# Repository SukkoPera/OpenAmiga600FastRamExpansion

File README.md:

# OpenAmiga600FastRamExpansion
OpenAmiga600FastRamExpansion is an Open Hardware 4 MB Fast RAM Expansion for the Commodore Amiga 600 Computer.

### Summary
Most low-end Amiga models only came with *Chip RAM*. "Big Box" models allowed for a different type of memory to be installed, known as *Fast RAM*, where *fast* means that it's dedicated to the main processor, so that it doesn't have to compete with the other chips in order to gain access to it (as is the case with Chip RAM). While both Chip and Fast RAM are limited in size, you can have at least a few MB of the latter on all Amigas (usually up to 8), while the former can never exceed 2 MB.

OpenAmiga600FastRamExpansion will allow you to add 4 MB of Fast RAM to your Amiga 600. This way you will be able to run more applications at once and more quickly. If you combine it with [a chip RAM expansion](https://github.com/SukkoPera/OpenAmiga600RamExpansion), you will also be able to run almost all games supported by WHDLoad, pushing the smallest of the Amigas to its limits. The Fast RAM will be mapped to `$200000-$5fffff`, which means it will not interfere with the PCMCIA address space.

Note that the A600 was not originally designed to support a Fast RAM expansion, which means Commodore didn't provide any connector for it. In theory it could be sandwiched between the CPU and mainboard, as usually done on A500s, but in the A600 the CPU is soldered directly to the mainboard and cannot be removed. Thus the only way to install it is to clip it over the CPU, using a PLCC socket placed upside-down. PLCC sockets are not meant to be used this way, so this is really a bit of a hack and might not even work in all cases. Space around the CPU is quite limited, hence the odd shape of this board.

OpenAmiga600FastRamExpansion is basically a clone of [a RAM expansion produced by Kipper2K a few years ago](http://eab.abime.net/showthread.php?t=64218), based on [an earlier design by lvd/NedoPC](http://lvd.nedopc.com/Projects/a600_8mb/index.html). He has since stopped producing and selling these cards and I thought it was a pity that he didn't open his designs and actually took all of them down, as this card is quite cheap to build and really useful. So I set about recreating it from scratch. Kipper2K has also made other expansions, including an 8 MB version of this card, but I chose to work on this one as it was simpler and probably enough for most uses. Other cards might come in the future.

### Memory Compatibility
The required RAM Type is 16 Mbit (1M×16) DRAM in the SOJ-42 package with up to 70-80 ns access time. It is 5v-only DRAM (not SDRAM!) often found in old 72-pin SIMMs, EDO chips might work or not. All chips having *8160* in their part number should be OK.

See [OpenAmiga500FastRamExpansion](https://github.com/SukkoPera/OpenAmiga500FastRamExpansion#memory-compatibility) for a compatibility list.

### Assembly and Installation
Open your A600, doing your best not to crack any of the small tabs that hold the case together. If your A600 has the top part of the shielding, remove it and store it somewhere, as you will not be able to put it back in place when the expansion is installed. The same goes for the HD cradle, sorry.

Lots of A600s (and of A1200s, for the record) have issues with leaking electrolytic capacitors, therefore I really recommend to inspect them first, while you have your Amiga open. They might be leaking even if your Amiga shows no problems and when it finally will, it might be too late (= expensive) to salvage it. So, if you notice any white or brownish marks around those shiny metal cylinders, get them replaced. It is NOT an easy thing to do and you need some decent tools anyway, so I really recommend to contact a professional, there are many people on Amiga forums offering this kind of service.

I suggest soldering the RAM chips first: these can either be soldered directly to the board or installed in sockets. While soldering the chips might not be trivial for the unexperienced, sockets for the SOJ-42 package are hard to find and not really easier to solder either, so the choice is up to you.

Next you should solder all the remaining surface mount components, first on the top side and then on the bottom side. Keep the CPLD and CPU socket last. Normally it is not necessary to mount all the decoupling capacitors for the RAM: I usually skip C4 and C7. Maybe capacitor C13 can be left out as well, your choice. R4 should be chosen according to the particular led you will be using for LD1. Actually you are free to skip LD1 and R4 altogether, if you hate power LEDs.

Before soldering the CPU socket you will need to rework it a bit if you want a really good fit: get some sandpaper and follow [these instructions](SocketRework.md). After it has been soldered, you can cut the bottom of it so that the window in the PCB continues through the socket. Most sockets will already have holes on the bottom that will make this operation easier. This will allow you to install a 14x14mm heatsink on the CPU, which might be a good idea since placing this board over the CPU will somewhat reduce the heat dissipation capabilities of the chip. Make sure to use good thermal adhesive/glue, otherwise you risk to make the dissipation even worse.

When you are done with the soldering you will need to program the CPLD. Whenever you do so, **make sure to carefully remove the board from your Amiga, or you might risk damaging it**. You can find the firmware [here](https://github.com/SukkoPera/OpenAmiga500FastRamExpansion/tree/master/firmware), along with instructions on how to flash it. Make sure you use the 4 MB version! You can provide power through the pads of C13 if you need to do so.

You are finally ready to install the expansion in your A600 but, before you do this, I suggest to clean the CPU pins using contact cleaner or isopropyl alcool and a toothbrush or cotton swabs, as all sorts of gunk will have probably gathered on them over the years. Let them dry well, then place the expansion over the CPU with the correct orientation and push it down firmly until it feels solidly in place. There should be no need to use the Force&trade;.

Before reassembling your case, I recommend to run [SysTest/Amiga Test Kit](https://github.com/keirf/Amiga-Stuff). Use the Memory option (<kbd>F1</kbd>), it must show 4 MB of Fast RAM. Then start the Memory Test (<kbd>F1</kbd> again) and let it run for 50-100 rounds: if it doesn't find any errors, you are probably good to go. If you get any errors, power off your computer and try to give the expansion a better fit, by pushing it further down or slightly twisting it back and forth.

It might happen that the board slowly works its way out of the socket over time. To avoid this you can anchor it to the mainboard using the hole to the left of the CPU, which should align with one of the holes for the HD cradle legs. If you have a 3D printer, another option is using [this nice frame designed by blekihun](https://www.thingiverse.com/thing:4824656).

Note that, as already mentioned, PLCC sockets are not meant to be used this way, which means that the contact quality degrades a bit with every insertion or removal of the board. So, try not to remove it unnecessarily. If you find that the contact has degraded so much that the machine is no longer stable, replace the socket with a new one.

### License
The OpenAmiga600FastRamExpansion documentation, including the design itself, is copyright &copy; SukkoPera 2019.

OpenAmiga600FastRamExpansion is Open Hardware licensed under the [CERN OHL v. 1.2](http://ohwr.org/cernohl).

You may redistribute and modify this documentation under the terms of the CERN OHL v.1.2. This documentation is distributed *as is* and WITHOUT ANY EXPRESS OR IMPLIED WARRANTIES whatsoever with respect to its functionality, operability or use, including, without limitation, any implied warranties OF MERCHANTABILITY, SATISFACTORY QUALITY, FITNESS FOR A PARTICULAR PURPOSE or infringement. We expressly disclaim any liability whatsoever for any direct, indirect, consequential, incidental or special damages, including, without limitation, lost revenues, lost profits, losses resulting from business interruption or loss of data, regardless of the form of action or legal theory under which the liability may be asserted, even if advised of the possibility or likelihood of such damages.

A copy of the full license is included in file [LICENSE.pdf](LICENSE.pdf), please refer to it for applicable conditions. In order to properly deal with its terms, please see file [LICENSE_HOWTO.pdf](LICENSE_HOWTO.pdf).

The contact points for information about manufactured Products (see section 4.2) are listed in file [PRODUCT.md](PRODUCT.md).

Any modifications made by Licensees (see section 3.4.b) shall be recorded in file [CHANGES.md](CHANGES.md).

The Documentation Location of the original project is https://github.com/SukkoPera/OpenAmiga600FastRamExpansion/.

### Support the Project
Since the project is open you are free to get the PCBs made by your preferred manufacturer, however in case you want to support the development, you can order them from PCBWay through this link:

You get my gratitude and cheap, professionally-made and good quality PCBs, I get some credit that will help with this and [other projects](https://www.pcbway.com/project/member/shareproject/?bmbid=41100). You won't even have to worry about the various PCB options, it's all pre-configured for you!

Also, if you still have to register to that site, [you can use this link](https://www.pcbway.com/setinvite.aspx?inviteid=41100) to get some bonus initial credit (and yield me some more).

Again, if you want to use another manufacturer, feel free to, don't feel obligated :). But then you can buy me a coffee if you want:

### Thanks
- lvd for the initial design
- Kipper2K for making his boards
- majinga for helping with the testing

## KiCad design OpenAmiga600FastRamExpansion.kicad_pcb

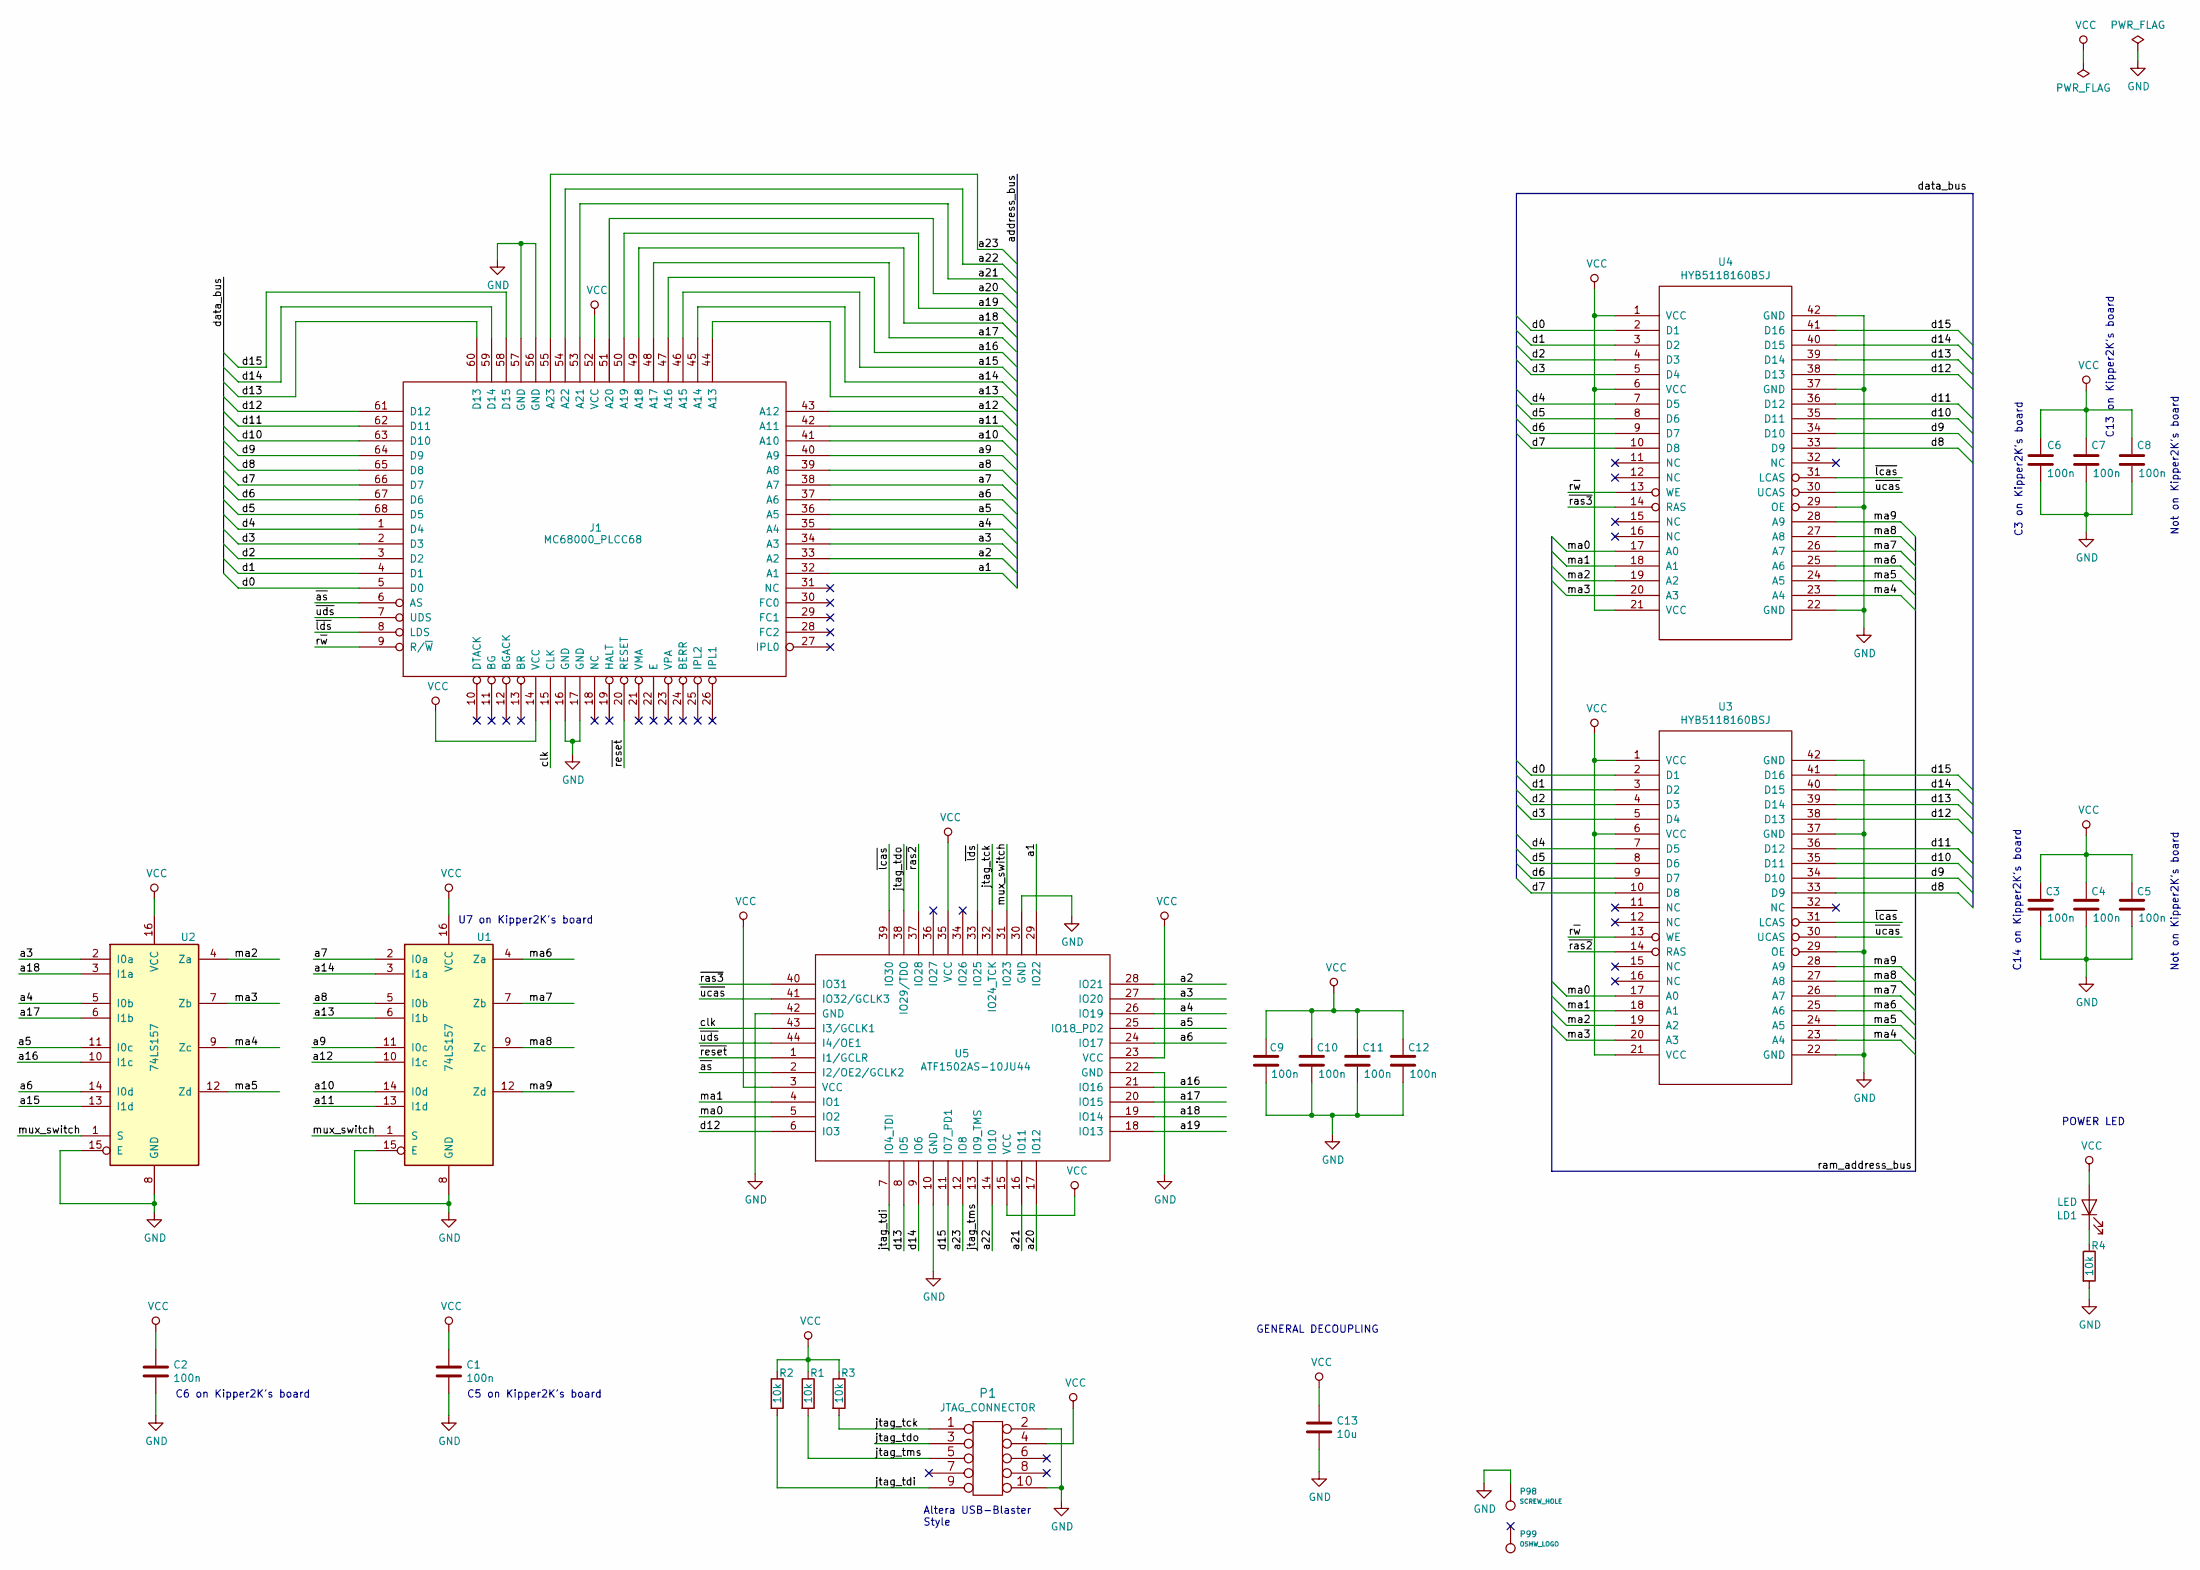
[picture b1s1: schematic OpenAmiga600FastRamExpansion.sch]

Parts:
C1, C2, C3, C4, C5, C6, C7, C8, C9, C10, C11, C12: 100n; C_0805_2012Metric_Pad1.15x1.40mm_HandSolder
C13: 10u; CP_Radial_D5.0mm_P2.00mm
J1: MC68000_PLCC68; PLCC-68_THT-SocketUpsideDown
LD1: LED; LED_0805_HandSoldering_ModSilkS
P1: JTAG_CONNECTOR; IDC-Header_2x05_P2.54mm_Vertical
P98: SCREW_HOLE; MountingHole_2.5mm_Pad_Via
P99: OSHW_LOGO; OSHW-Logo2_7.3x6mm_Copper
R1, R2, R3, R4: 10k; R_0805_2012Metric_Pad1.15x1.40mm_HandSolder
U1, U2: 74LS157; SOIC-16_3.9x9.9mm_P1.27mm
U3, U4: HYB5118160BSJ; SOJ-42-LongPads
U5: ATF1502AS-10JU44; PLCC-44_THT-Socket

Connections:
/a1: J1.32 (A1), U5.29 (IO22)
/a2: J1.33 (A2), U5.28 (IO21)
/a3: J1.34 (A3), U2.2 (I0a), U5.27 (IO20)
/a4: J1.35 (A4), U2.5 (I0b), U5.26 (IO19)
/a5: J1.36 (A5), U2.11 (I0c), U5.25 (IO18_PD2)
/a6: J1.37 (A6), U2.14 (I0d), U5.24 (IO17)
/a7: J1.38 (A7), U1.2 (I0a)
/a8: J1.39 (A8), U1.5 (I0b)
/a9: J1.40 (A9), U1.11 (I0c)
/a10: J1.41 (A10), U1.14 (I0d)
/a11: J1.42 (A11), U1.13 (I1d)
/a12: J1.43 (A12), U1.10 (I1c)
/a13: J1.44 (A13), U1.6 (I1b)
/a14: J1.45 (A14), U1.3 (I1a)
/a15: J1.46 (A15), U2.13 (I1d)
/a16: J1.47 (A16), U2.10 (I1c), U5.21 (IO16)
/a17: J1.48 (A17), U2.6 (I1b), U5.20 (IO15)
/a18: J1.49 (A18), U2.3 (I1a), U5.19 (IO14)
/a19: J1.50 (A19), U5.18 (IO13)
/a20: J1.51 (A20), U5.17 (IO12)
/a21: J1.53 (A21), U5.16 (IO11)
/a22: J1.54 (A22), U5.14 (IO10)
/a23: J1.55 (A23), U5.12 (IO8)
/clk: J1.15 (CLK), U5.43 (I3/GCLK1)
/d0: J1.5 (D0), U3.2 (D1), U4.2 (D1)
/d1: J1.4 (D1), U3.3 (D2), U4.3 (D2)
/d2: J1.3 (D2), U3.4 (D3), U4.4 (D3)
/d3: J1.2 (D3), U3.5 (D4), U4.5 (D4)
/d4: J1.1 (D4), U3.7 (D5), U4.7 (D5)
/d5: J1.68 (D5), U3.8 (D6), U4.8 (D6)
/d6: J1.67 (D6), U3.9 (D7), U4.9 (D7)
/d7: J1.66 (D7), U3.10 (D8), U4.10 (D8)
/d8: J1.65 (D8), U3.33 (D9), U4.33 (D9)
/d9: J1.64 (D9), U3.34 (D10), U4.34 (D10)
/d10: J1.63 (D10), U3.35 (D11), U4.35 (D11)
/d11: J1.62 (D11), U3.36 (D12), U4.36 (D12)
/d12: J1.61 (D12), U3.38 (D13), U4.38 (D13), U5.6 (IO3)
/d13: J1.60 (D13), U3.39 (D14), U4.39 (D14), U5.8 (IO5)
/d14: J1.59 (D14), U3.40 (D15), U4.40 (D15), U5.9 (IO6)
/d15: J1.58 (D15), U3.41 (D16), U4.41 (D16), U5.11 (IO7_PD1)
/jtag_tck: P1.1, R3.2, U5.32 (IO24_TCK)
/jtag_tdi: P1.9, R2.2, U5.7 (IO4_TDI)
/jtag_tdo: P1.3, U5.38 (IO29/TDO)
/jtag_tms: P1.5, R1.2, U5.13 (IO9_TMS)
/ma0: U3.17 (A0), U4.17 (A0), U5.5 (IO2)
/ma1: U3.18 (A1), U4.18 (A1), U5.4 (IO1)
/ma2: U2.4 (Za), U3.19 (A2), U4.19 (A2)
/ma3: U2.7 (Zb), U3.20 (A3), U4.20 (A3)
/ma4: U2.9 (Zc), U3.23 (A4), U4.23 (A4)
/ma5: U2.12 (Zd), U3.24 (A5), U4.24 (A5)
/ma6: U1.4 (Za), U3.25 (A6), U4.25 (A6)
/ma7: U1.7 (Zb), U3.26 (A7), U4.26 (A7)
/ma8: U1.9 (Zc), U3.27 (A8), U4.27 (A8)
/ma9: U1.12 (Zd), U3.28 (A9), U4.28 (A9)
/mux_switch: U1.1 (S), U2.1 (S), U5.31 (IO23)
/r~w: J1.9 (R/~W), U3.13 (WE), U4.13 (WE)
/~as: J1.6 (AS), U5.2 (I2/OE2/GCLK2)
/~lcas: U3.31 (LCAS), U4.31 (LCAS), U5.39 (IO30)
/~lds: J1.8 (LDS), U5.33 (IO25)
/~ras2: U3.14 (RAS), U5.37 (IO28)
/~ras3: U4.14 (RAS), U5.40 (IO31)
/~reset: J1.20 (RESET), U5.1 (I1/GCLR)
/~ucas: U3.30 (UCAS), U4.30 (UCAS), U5.41 (IO32/GCLK3)
/~uds: J1.7 (UDS), U5.44 (I4/OE1)
GND: C1.2, C2.2, C3.2, C4.2, C5.2, C6.2, C7.2, C8.2, C9.2, C10.2, C11.2, C12.2, C13.2, J1.16 (GND), J1.17 (GND), J1.56 (GND), J1.57 (GND), P1.2, P1.10, P98.1, R4.2, U1.8 (GND), U1.15 (E), U2.8 (GND), U2.15 (E), U3.22 (GND), U3.29 (OE), U3.37 (GND), U3.42 (GND), U4.22 (GND), U4.29 (OE), U4.37 (GND), U4.42 (GND), U5.10 (GND), U5.22 (GND), U5.30 (GND), U5.42 (GND)
unnamed: LD1.1 (K), R4.1
VCC: C1.1, C2.1, C3.1, C4.1, C5.1, C6.1, C7.1, C8.1, C9.1, C10.1, C11.1, C12.1, C13.1, J1.14 (VCC), J1.52 (VCC), LD1.2 (A), P1.4, R1.1, R2.1, R3.1, U1.16 (VCC), U2.16 (VCC), U3.1 (VCC), U3.6 (VCC), U3.21 (VCC), U4.1 (VCC), U4.6 (VCC), U4.21 (VCC), U5.3 (VCC), U5.15 (VCC), U5.23 (VCC), U5.35 (VCC)

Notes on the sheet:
Altera USB-Blaster Style
U7 on Kipper2K's board
C5 on Kipper2K's board
C6 on Kipper2K's board
C14 on Kipper2K's board
Not on Kipper2K's board
C3 on Kipper2K's board
C13 on Kipper2K's board
GENERAL DECOUPLING
POWER LED

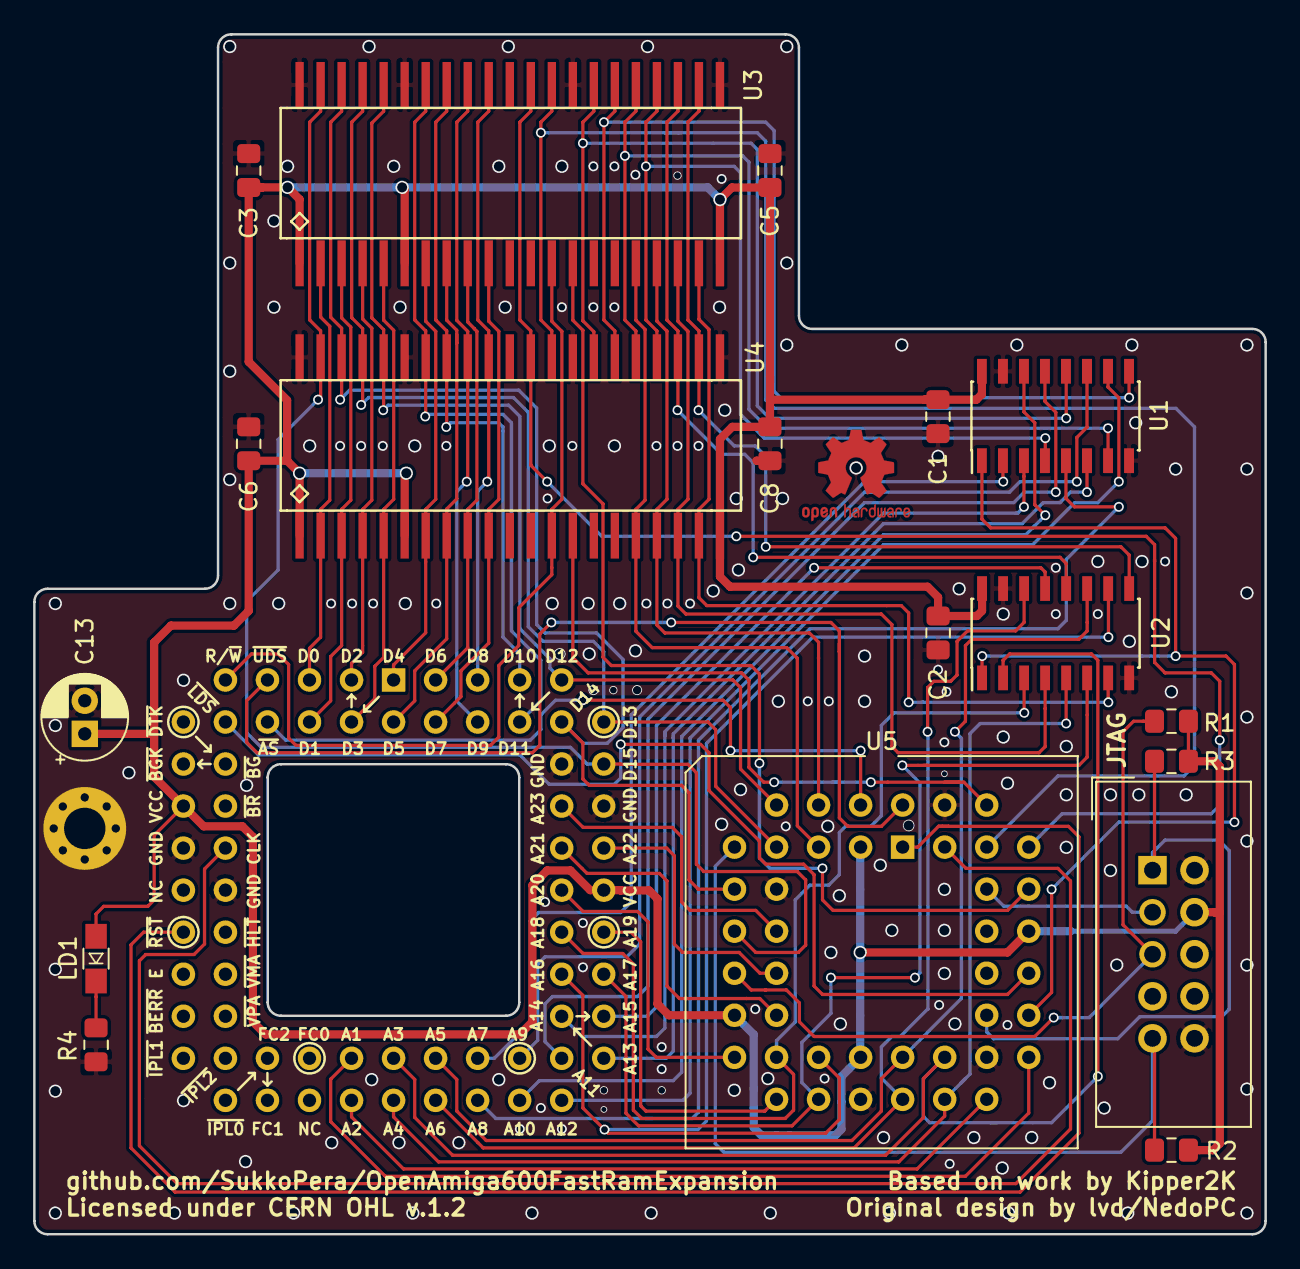
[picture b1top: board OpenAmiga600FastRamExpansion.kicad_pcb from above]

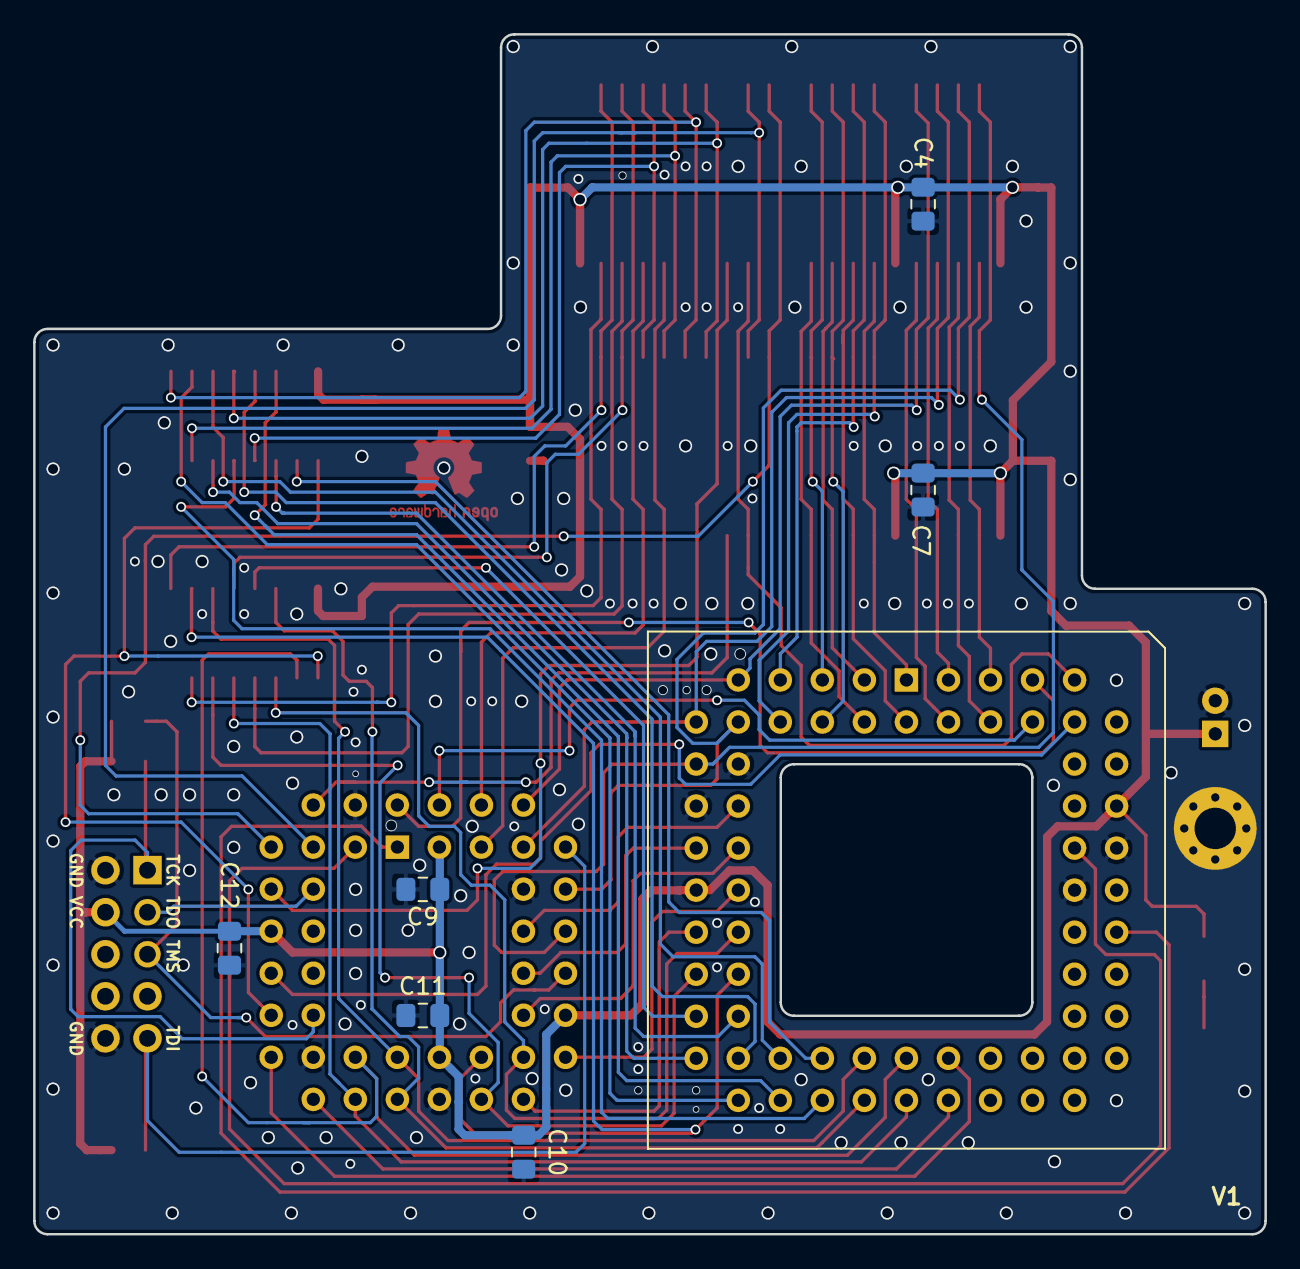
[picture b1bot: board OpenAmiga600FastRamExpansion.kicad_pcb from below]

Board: 2 copper layers, 74.4 x 72.5 mm, 27 parts (6 on the bottom side), 67 nets.

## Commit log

2019-02-18 Add .gitignore
2019-02-18 Schematic is complete
2019-02-18 Ready for routing!
2019-02-18 Final disposition?
2019-02-19 Make C13 THT and remove C14
2019-02-19 Routing in progress...
2019-02-21 Routing in progress... (Part II)
2019-02-21 Routing almost done, only power TBD Also added 3D models for all components
2019-02-22 Add schematics PDF
2019-02-22 Add license
2019-02-22 Routing complete Still needs some refinements
2019-02-22 Move socket contour to bottom silkscreen
2019-02-24 Stitching ground planes
2019-02-26 Ground stitching done
2019-02-26 More stitching
2019-02-26 More and more stitching
2019-02-26 More and more and more stitching
2019-02-26 Minor refinements
2019-02-26 Connect screw hole to ground plate
2019-02-26 Add version number and update renders
2019-02-27 Add JTAG pinout
2019-03-03 Make ground stitching vias net size
2019-03-03 Use real IDC-10 connector for JTAG
2019-03-03 Add via
2019-03-03 Update renders
2019-05-19 Fix #1
2019-05-19 Fix #2
2019-05-19 Ready for V1
2019-08-19 Close #3
2019-08-19 Add note about how to provide power during flashing
2019-11-04 Add socket rework guide
2019-11-08 Some rewording
2021-04-12 Add link to 3D-printable frame
2026-02-13 Change coffee donation link image in README
    Updated the coffee donation link image in the README.

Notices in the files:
OpenAmiga600FastRamExpansion.kicad_pcb:
Licensed under CERN OHL v.1.2
